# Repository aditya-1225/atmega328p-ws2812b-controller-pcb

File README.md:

# PCB – ATmega328P WS2812B Controller

This PCB uses an ATmega328P microcontroller to control an addressable WS2812B LED strip.

## Controls
The PCB includes three push buttons:
1. Increase LED brightness  
2. Decrease LED brightness  
3. Change the LED pattern

## Connections
- The LED strip connects to the PCB via a screw terminal (J1).
- The board is programmed using an 8-pin header connector (J2).

## License
CERN Open Hardware Licence Version 2 - Permissive

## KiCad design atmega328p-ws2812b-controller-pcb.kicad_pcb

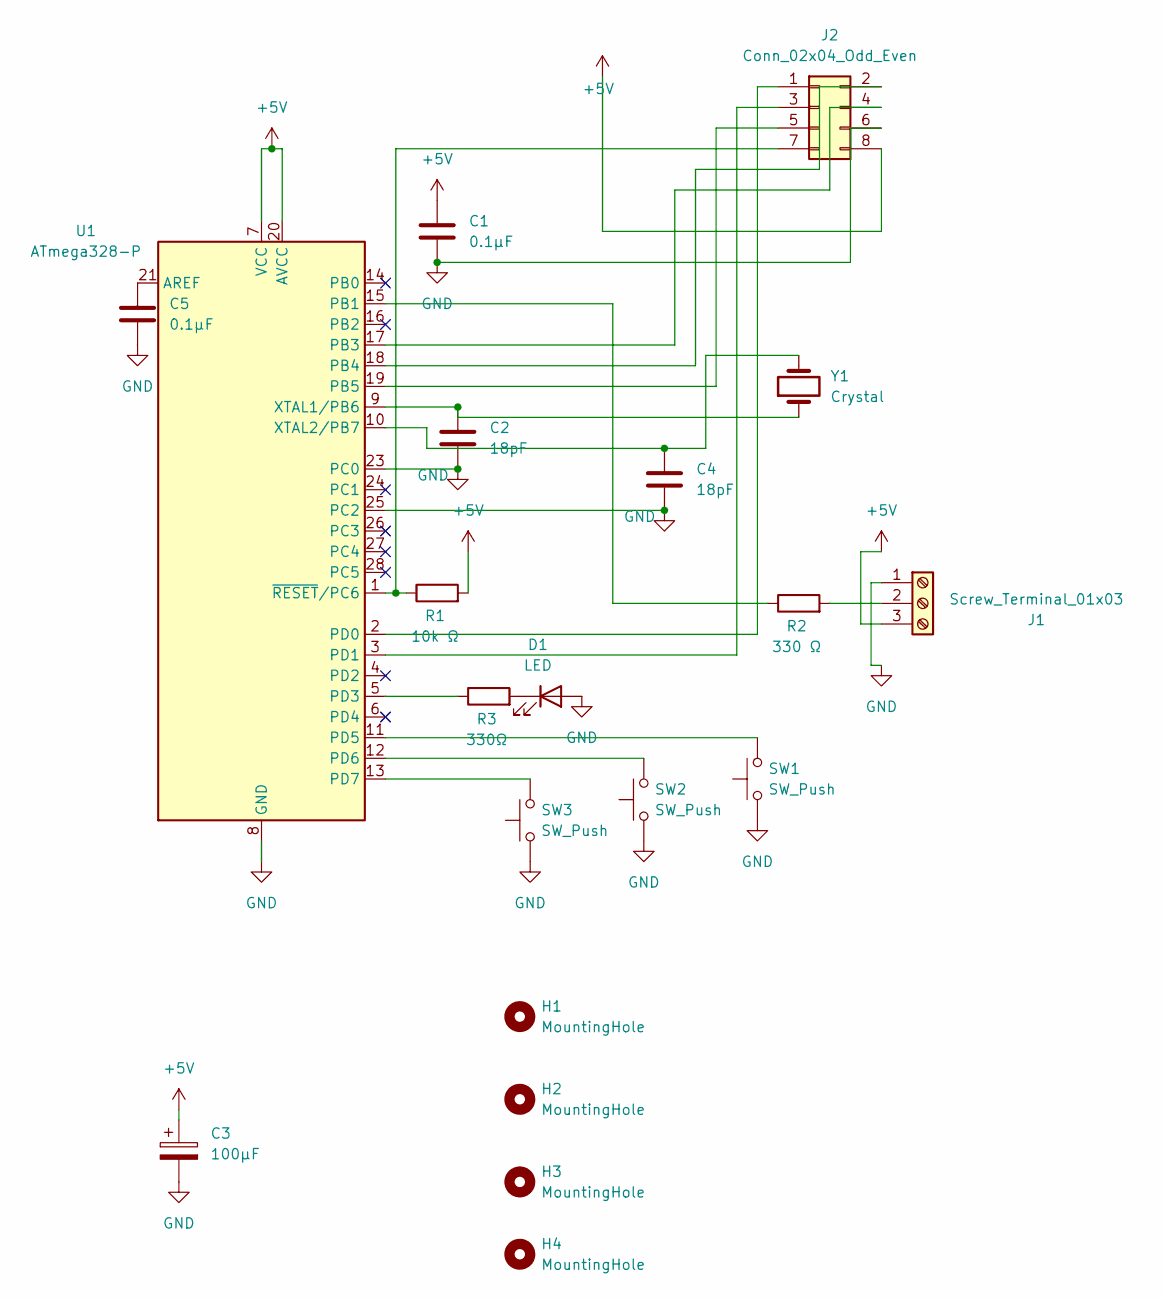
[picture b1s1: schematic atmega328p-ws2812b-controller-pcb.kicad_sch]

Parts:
C1, C5: 0.1μF; C_1206_3216Metric_Pad1.33x1.80mm_HandSolder
C2, C4: 18pF; C_1206_3216Metric_Pad1.33x1.80mm_HandSolder
C3: 100μF; CP_Radial_D5.0mm_P2.00mm
D1: LED; LED_1206_3216Metric_Pad1.42x1.75mm_HandSolder
H1, H2, H3, H4: MountingHole; MountingHole_2mm
J1: Screw_Terminal_01x03; TerminalBlock_MaiXu_MX126-5.0-03P_1x03_P5.00mm
J2: Conn_02x04_Odd_Even; PinHeader_2x04_P2.54mm_Vertical
R1: 10k Ω; R_1206_3216Metric_Pad1.30x1.75mm_HandSolder
R2: 330 Ω; R_1206_3216Metric_Pad1.30x1.75mm_HandSolder
R3: 330Ω; R_1206_3216Metric_Pad1.30x1.75mm_HandSolder
SW1, SW2, SW3: SW_Push; SW_PUSH-12mm
U1: ATmega328-P; DIP-28_W7.62mm_Socket
Y1: Crystal; Crystal_HC49-U_Vertical

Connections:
+5V: C1.1, C3.1, J1.3, J2.8, R1.2, U1.7 (VCC), U1.20 (AVCC)
GND: C1.2, C2.2, C3.2, C4.2, C5.2, D1.2 (A), J1.1, J2.6, SW1.1, SW2.1, SW3.1, U1.8 (GND), U1.22 (GND), U1.23 (PC0), U1.25 (PC2)
unnamed: D1.1 (K), R3.2
unnamed: J1.2, R2.2
unnamed: J2.1, U1.2 (PD0)
unnamed: J2.2, U1.18 (PB4)
unnamed: J2.3, U1.3 (PD1)
unnamed: J2.4, U1.17 (PB3)
unnamed: J2.5, U1.19 (PB5)
unnamed: J2.7, R1.1, U1.1 (~RESET/PC6)
unnamed: C5.1, U1.21 (AREF)
unnamed: R2.1, U1.15 (PB1)
unnamed: R3.1, U1.5 (PD3)
unnamed: SW1.2, U1.11 (PD5)
unnamed: SW2.2, U1.12 (PD6)
unnamed: SW3.2, U1.13 (PD7)
unnamed: C2.1, U1.9 (XTAL1/PB6), Y1.1
unnamed: C4.1, U1.10 (XTAL2/PB7), Y1.2

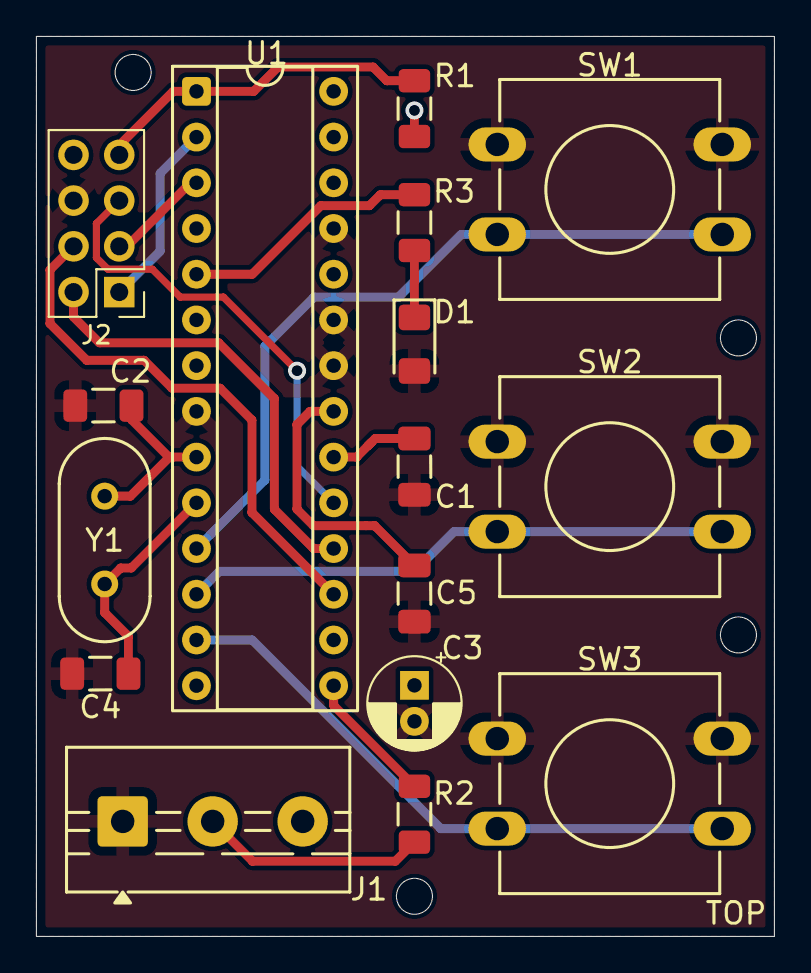
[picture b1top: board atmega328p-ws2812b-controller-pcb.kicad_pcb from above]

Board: 2 copper layers, 41.0 x 50.0 mm, 20 parts (0 on the bottom side), 18 nets.

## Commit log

2026-01-16 Renamed files, Added README and LICENSE
2026-01-16 Reorganize project directory structure
